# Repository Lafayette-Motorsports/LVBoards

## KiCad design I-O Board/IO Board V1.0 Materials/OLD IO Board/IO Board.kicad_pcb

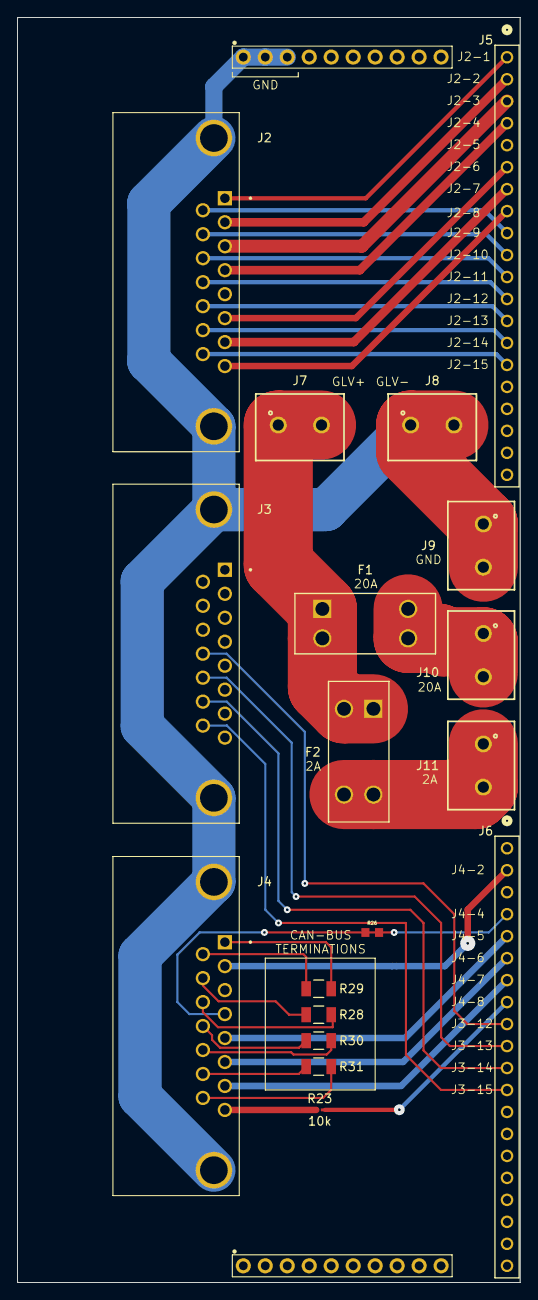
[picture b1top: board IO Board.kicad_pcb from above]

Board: 2 copper layers, 58.1 x 146.2 mm, 19 parts (0 on the bottom side), 36 nets.

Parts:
F1: 20A; 3568_KEY
F2: 2A; 3568_KEY
J1: PH1-10-UA; 1X10-2.54MM-THT
J2, J3, J4: *; AMPHENOL_L717SDA15P1ACH4F
J5, J6: 20-0600-21; CONN_20-0600-21_ARS
J7, J8, J9, J10, J11: 691137710002
R23: 10k; RES_RMCF0201_STP
R26: 3.01k; RESC1608X55N
R28, R29, R30, R31: 120; RES_TNPW1206_VIS

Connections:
unnamed: F1.1, F1.2, F2.1, F2.2, J7.1, J7.2
unnamed: F1.3, F1.4, J10.1, J10.2
unnamed: F2.3, F2.4, J11.1, J11.2
unnamed: J1.1, J1.2, J1.3, J2.S1 (SHIELD), J2.S2 (SHIELD), J3.S1 (SHIELD), J3.S2 (SHIELD), J4.S1 (SHIELD), J4.S2 (SHIELD), J8.1, J8.2, J9.1, J9.2
unnamed: J2.01, J5.1
unnamed: J2.02, J5.2
unnamed: J2.03, J5.3
unnamed: J2.04, J5.4
unnamed: J2.06, J5.6
unnamed: J2.07, J5.7
unnamed: J2.08, J5.8
unnamed: J2.09, J5.9
unnamed: J2.10, J5.10
unnamed: J2.11, J5.11
unnamed: J2.12, J5.12
unnamed: J2.13, J5.13
unnamed: J2.14, J5.14
unnamed: J2.15, J5.15
unnamed: J3.12, J6.9
unnamed: J3.13, J6.10
unnamed: J3.14, J6.11
unnamed: J3.15, J6.12
unnamed: J4.01, R29.1
unnamed: J4.04, J6.4, R26.1, R26.2
unnamed: J4.05, J6.5
unnamed: J4.06, J6.6
unnamed: J4.07, J6.7
unnamed: J4.08, R23.1
unnamed: J4.09, R29.2
unnamed: J4.10, R28.1
unnamed: J4.11, R28.2
unnamed: J4.12, R30.1
unnamed: J4.13, R30.2
unnamed: J4.14, R31.1
unnamed: J4.15, R31.2
unnamed: J6.8, R23.2

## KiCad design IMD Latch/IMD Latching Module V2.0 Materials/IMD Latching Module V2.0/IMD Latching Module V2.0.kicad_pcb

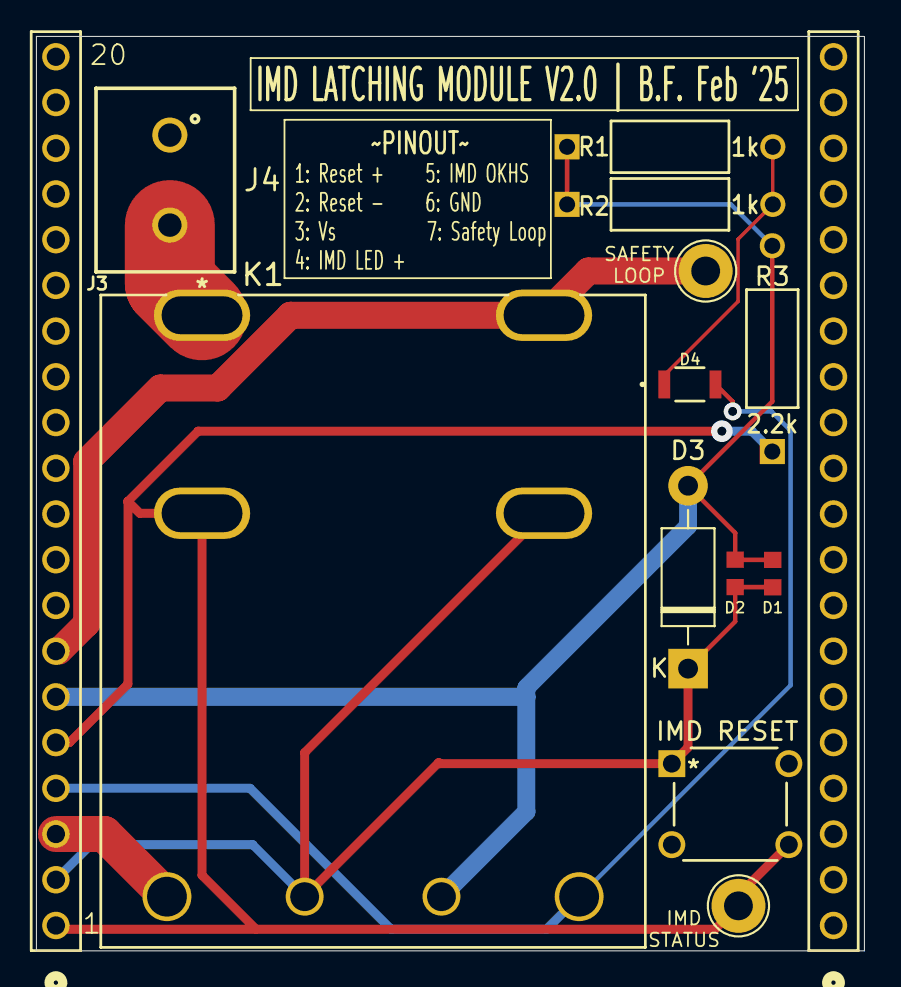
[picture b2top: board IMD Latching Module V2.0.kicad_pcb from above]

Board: 2 copper layers, 46.0 x 50.8 mm, 14 parts (0 on the bottom side), 8 nets.

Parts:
D1, D2: D_Zener; RESC1508X55N
D3: 1N4001; D_DO-41_SOD81_P10.16mm_Horizontal
D4: LED (Test); LED_AP3216SYD_KNB-L
IMD RESET: Test Reset IMD; SW4_1825910-B_TEC
J2, J3: PH1-20-UA; CONN_PH1-20-UA_ADM
J4: 691137710002
K1: AHES4291; AHES4_PAN
R1, R2: 1k; STA_CF14_STP
R3: 2.2k; STA_CF14_STP
TP1, TP2: TestPoint; TestPoint_Loop_D2.60mm_Drill1.6mm_Beaded

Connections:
/GND: D1.2 (A), D2.2 (A), D3.2 (A), J3.6, K1.5, R1.1, R2.1, R3.2
/Vs: J3.3, K1.3
unnamed: D1.1 (K), D2.1 (K), D3.1 (K), IMD RESET.1, J3.2, K1.4, K1.7
unnamed: D4.2 (A), J3.4, K1.6
unnamed: D4.1 (K), R1.2, R2.2
unnamed: IMD RESET.4, J3.1, J3.5, K1.2, R3.1, TP1.1
unnamed: J3.7, K1.8, TP2.1
unnamed: J4.2, K1.1

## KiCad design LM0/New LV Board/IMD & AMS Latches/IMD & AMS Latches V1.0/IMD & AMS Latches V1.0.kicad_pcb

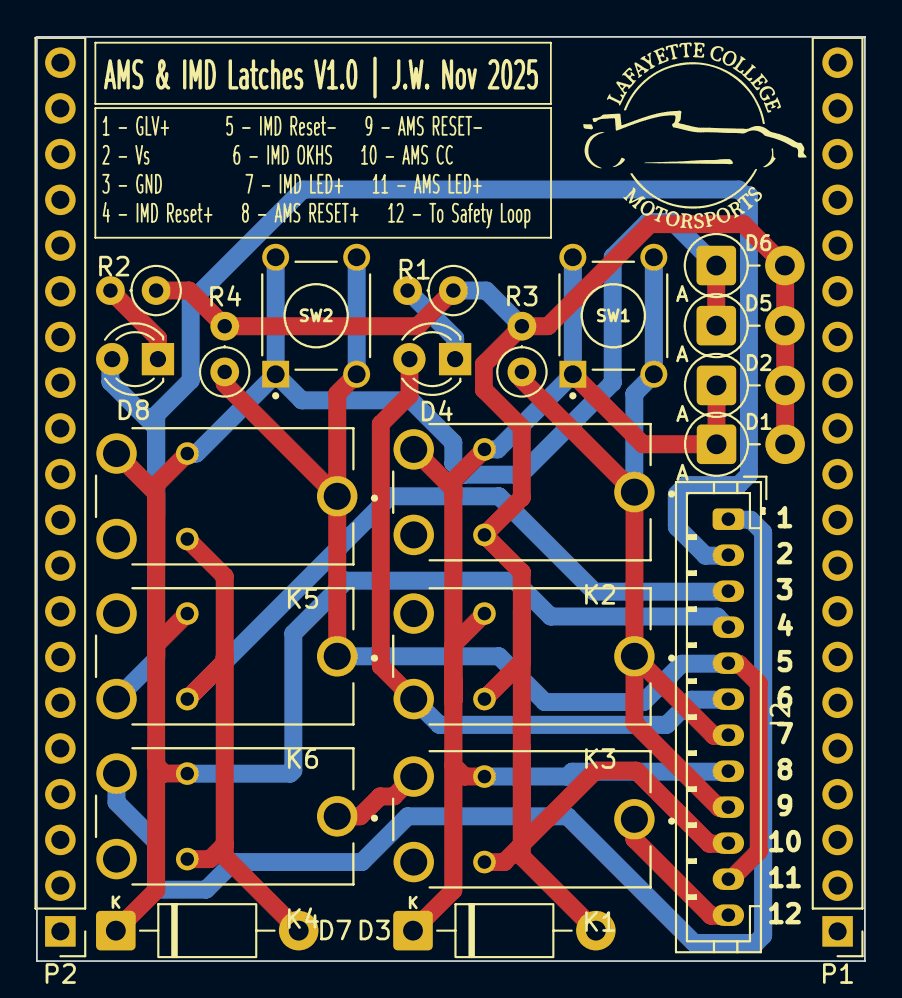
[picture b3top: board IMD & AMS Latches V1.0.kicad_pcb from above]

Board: 2 copper layers, 46.0 x 51.3 mm, 23 parts (0 on the bottom side), 13 nets.

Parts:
D1, D2, D5, D6: 1N4743A; D_DO-41_SOD81_P3.81mm_Vertical_AnodeUp
D3, D7: 1N4001; D_DO-41_SOD81_P10.16mm_Horizontal
D4, D8: LED (Test); LED_D3.0mm
J2: B12B-PH-K-S; JST_PH_B12B-PH-K_1x12_P2.00mm_Vertical
K1, K2, K3, K4, K5, K6: A161CS12VDC.64; RELAY_A161CS12VDC.64
P1, P2: PH1-20-UA; PinHeader_1x20_P2.54mm_Vertical
R1, R2: 680; R_Axial_DIN0207_L6.3mm_D2.5mm_P2.54mm_Vertical
R3, R4: 2.2k; R_Axial_DIN0207_L6.3mm_D2.5mm_P2.54mm_Vertical
SW1, SW2: Test Reset IMD; pushButton

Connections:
unnamed: D1.2 (A), D2.2 (A), D3.2 (A), D5.2 (A), D6.2 (A), J2.3, K1.A1, K2.A1, K3.A1, R1.1, R2.1, R3.2, R4.2
unnamed: D1.1 (K), D2.1 (K), D3.1 (K), J2.5, K1.A2, K2.A2, K2.NO, K3.A2, SW1.1
unnamed: D4.2 (A), J2.7, K3.NC
unnamed: D4.1 (K), R1.2
unnamed: D5.1 (K), D6.1 (K), D7.1 (K), J2.9, K4.A2, K5.A2, K5.NO, K6.A2, SW2.1
unnamed: D7.2 (A), J2.10, K4.A1, K5.A1, K6.A1
unnamed: D8.2 (A), J2.11, K6.NC
unnamed: D8.1 (K), R2.2
unnamed: J2.1, K1.COM
unnamed: J2.2, J2.8, K5.COM, K6.COM, R4.1, SW2.2
unnamed: J2.4, J2.6, K2.COM, K3.COM, R3.1, SW1.2
unnamed: J2.12, K4.NO
unnamed: K1.NO, K4.COM

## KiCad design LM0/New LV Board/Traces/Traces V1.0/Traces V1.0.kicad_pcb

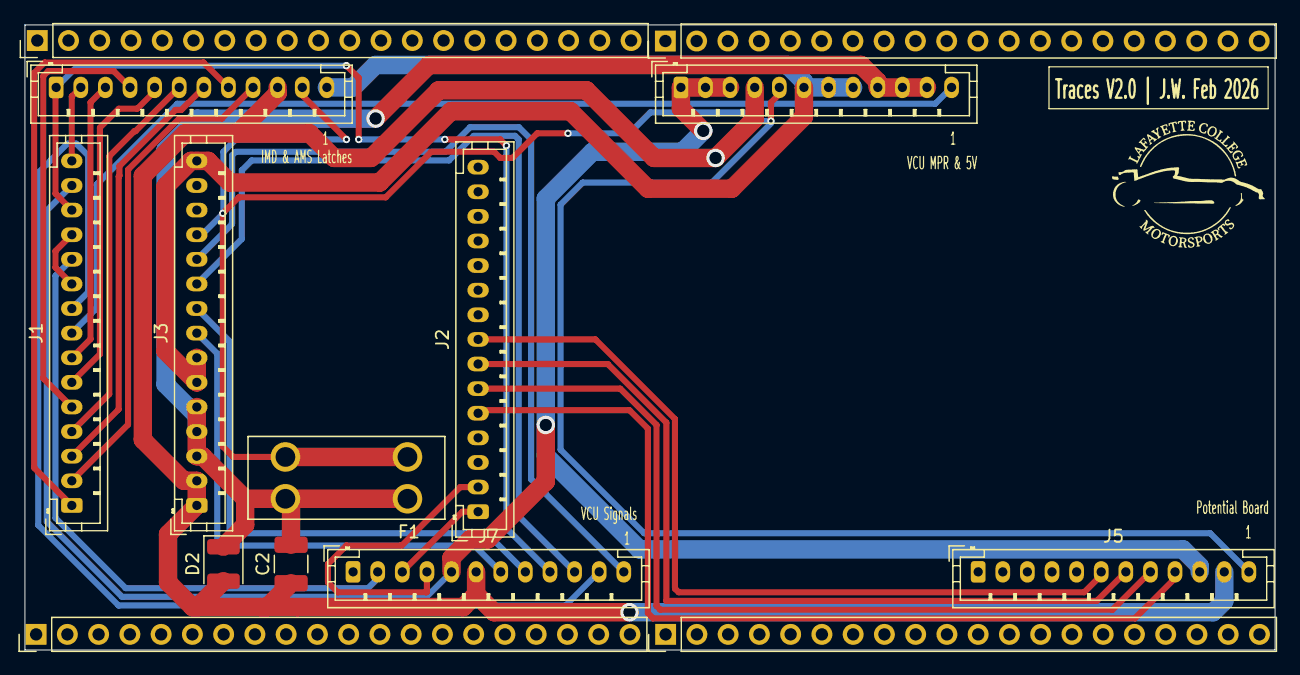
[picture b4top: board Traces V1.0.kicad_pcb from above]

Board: 2 copper layers, 101.6 x 50.8 mm, 10 parts (0 on the bottom side), 28 nets.

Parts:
C2: 47u; C_1210_3225Metric_Pad1.33x2.70mm_HandSolder
D2: D_Zener; D_1210_3225Metric
F1: 2A; FUSE_3568
J1, J2, J3: B15B-PH-K-S; JST_PH_B15B-PH-K_1x15_P2.00mm_Vertical
J4, J5, J6, J7: B12B-PH-K-S; JST_PH_B12B-PH-K_1x12_P2.00mm_Vertical

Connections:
unnamed: C2.1, D2.2 (A), J3.1, J3.2, J4.4, J5.11, J6.10, J7.6
unnamed: C2.2, D2.1 (K), F1.1, F1.2, J3.3, J3.4, J3.5, J4.9, J4.10, J4.11
unnamed: J1.10, J1.12
unnamed: J1.14, J4.1, J4.2, J4.3, J5.10, J7.5
unnamed: F1.3, F1.4, J3.12, J4.5, J5.12, J6.11
unnamed: J3.6, J3.7, J3.15, J4.6, J4.7, J4.8, J6.12
unnamed: J1.8, J4.12
unnamed: J2.8, J5.6
unnamed: J2.7, J5.7
unnamed: J2.6, J5.8
unnamed: J2.5, J5.9
unnamed: J1.13, J6.1, J7.9
unnamed: J1.15, J6.2
unnamed: J1.7, J6.3
unnamed: J1.5, J6.4
unnamed: J1.6, J6.5
unnamed: J1.4, J6.6
unnamed: J1.3, J6.7
unnamed: J1.1, J6.8
unnamed: J1.2, J6.9
unnamed: J1.11, J7.2
unnamed: J2.1, J7.3
unnamed: J2.2, J7.4
unnamed: J3.8, J7.7
unnamed: J3.9, J7.8
unnamed: J3.10, J7.10
unnamed: J1.9, J7.11
unnamed: J3.11, J7.12

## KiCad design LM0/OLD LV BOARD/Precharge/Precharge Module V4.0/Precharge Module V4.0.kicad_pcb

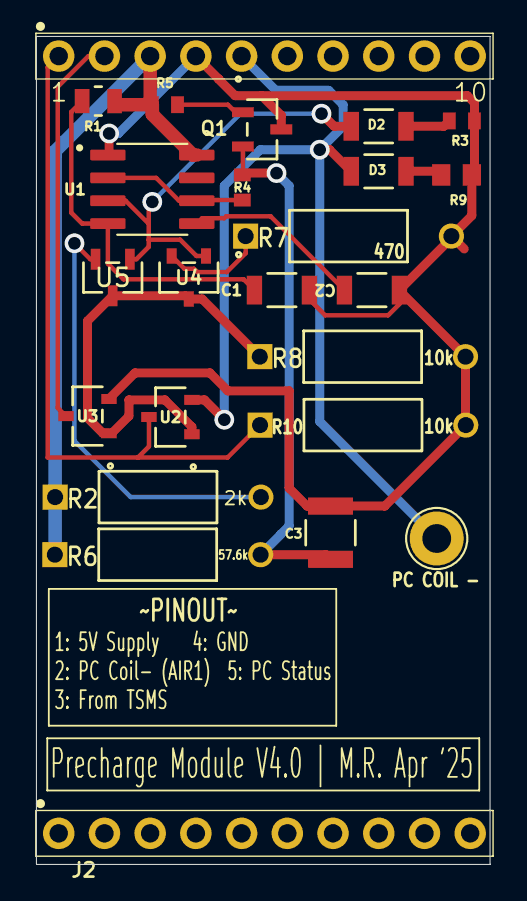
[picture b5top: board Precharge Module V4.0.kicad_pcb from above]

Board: 2 copper layers, 25.2 x 46.0 mm, 24 parts (0 on the bottom side), 16 nets.

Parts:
C1, C2: 0.1u; CAP_CL31_SAM
C3: 47u; CAP_CL32_SAM
D2: 3 second timer; LED_AP3216SYD_KNB
D3: LED (Test); LED_AP3216SYD_KNB
J1, J2: PH1-10-UA; 1X10-2.54MM-THT
PC COIL -: TestPoint; TestPoint_Loop_D2.60mm_Drill1.6mm_Beaded
Q1: SS8550; SOT-23_MCC
R1: 22k; STA_RMCF0805_STP
R2: 2k; STA_CF14_STP
R3, R4, R5: 1k; STA_RMCF0603_STP
R6: 57.6k; STA_CF14_STP
R7: 470; STA_CF14_STP
R8, R10: 10k; STA_CF14_STP
R9: 150R; RC0805N_YAG
U1: NE555D; SOIC127P599X175-8N
U2, U3, U4: IRLML2060TRPBF; SOT23_INF
U5: PMV160UP_NEX

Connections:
Drain: R8.1, U2.1 (G), U3.1 (G), U4.3 (D), U5.3
END: D3.2 (A), J1.5, PC COIL -.1, U2.2 (S)
Gate: D2.2 (A), U1.3 (Q), U4.1 (G), U5.1
unnamed: D2.1 (K), R3.1
unnamed: D3.1 (K), R9.2
unnamed: Q1.1 (B), R5.2
unnamed: C1.2, C2.2, C3.2, J1.4, Q1.3 (C), R3.2, R7.2, R8.2, R9.1, R10.2, U1.1 (GND), U3.2 (S)
unnamed: C3.1, Q1.2 (E), R4.2, R6.2
unnamed: C2.1, U1.5 (CV)
unnamed: C1.1, R1.1, U1.4 (R)
unnamed: R4.1, U1.2 (TR), U1.6 (THR)
unnamed: J1.3, R1.2, R2.1, R5.1, R6.1, U1.8 (VCC)
unnamed: J1.1, U2.3 (D)
unnamed: J1.2, U3.3 (D)
NmosSource: R7.1, U4.2 (S)
PMOSSOURCE: R2.2, U5.2
